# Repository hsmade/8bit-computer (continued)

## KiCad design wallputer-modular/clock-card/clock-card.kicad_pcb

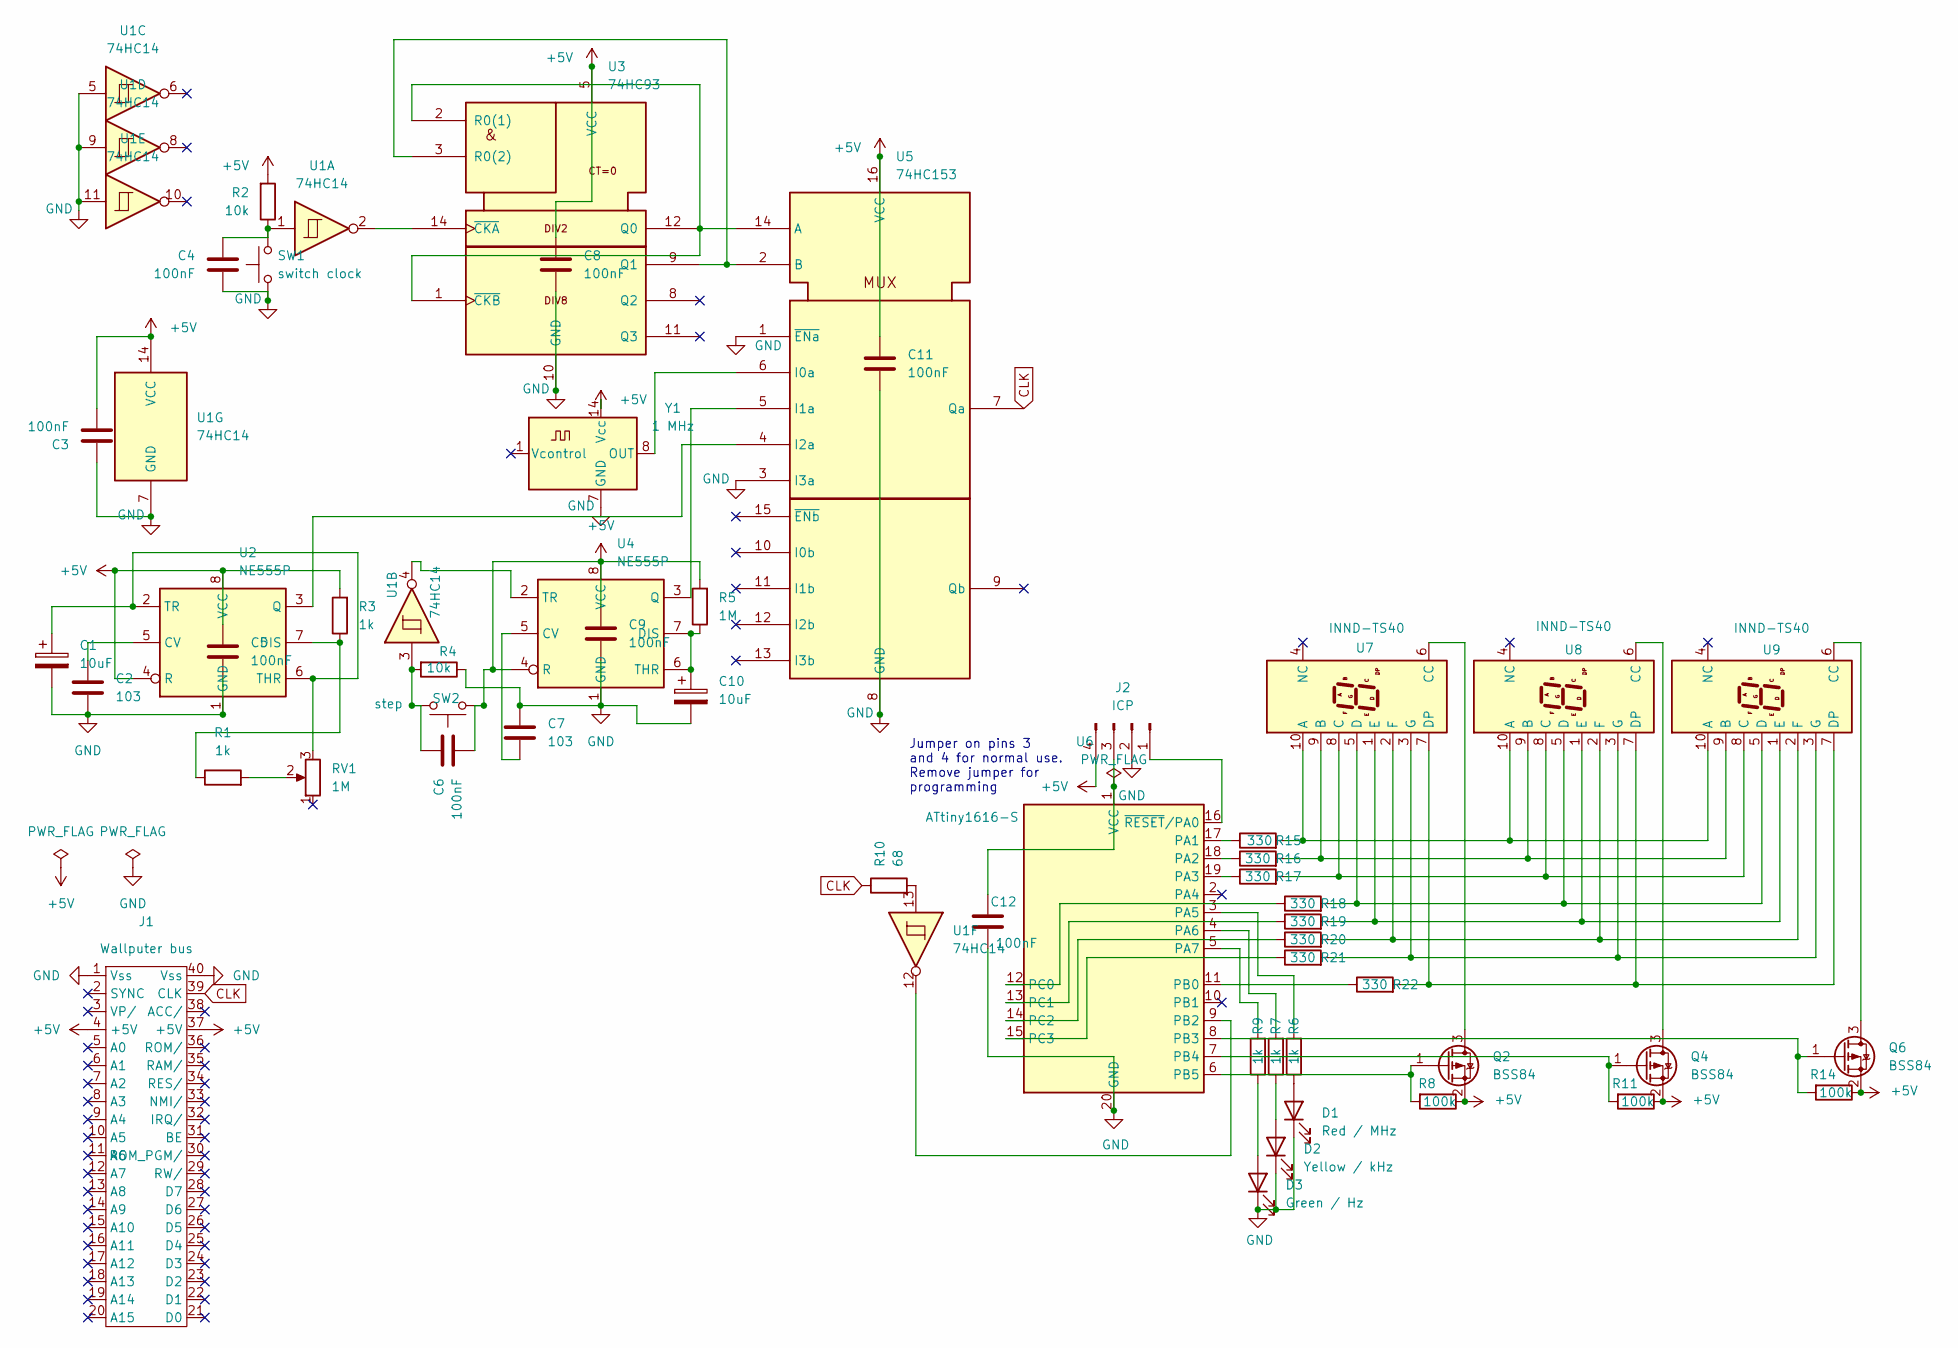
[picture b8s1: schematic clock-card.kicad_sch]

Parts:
C1, C10: 10uF; CP_Radial_D5.0mm_P2.00mm
C2, C7: 103; C_Disc_D5.0mm_W2.5mm_P5.00mm
C3, C4, C5, C6, C8, C9, C11, C12: 100nF; C_Disc_D5.0mm_W2.5mm_P5.00mm
D1: Red / MHz; LED_D1.8mm_W3.3mm_H2.4mm
D2: Yellow / kHz; LED_D1.8mm_W3.3mm_H2.4mm
D3: Green / Hz; LED_D1.8mm_W3.3mm_H2.4mm
J1: Wallputer_Bus_*
J2: ICP; PinHeader_1x04_P2.54mm_Vertical
Q2, Q4, Q6: BSS84; SOT-23
R1, R3: 1k; R_Axial_DIN0204_L3.6mm_D1.6mm_P2.54mm_Vertical
R2, R4: 10k; R_Axial_DIN0204_L3.6mm_D1.6mm_P2.54mm_Vertical
R5: 1M; R_Axial_DIN0204_L3.6mm_D1.6mm_P2.54mm_Vertical
R6, R7, R9: 1k; R_0603_1608Metric
R8, R11, R14: 100k; R_0603_1608Metric
R10: 68; R_0603_1608Metric
R15, R16, R17, R18, R19, R20, R21, R22: 330; R_0603_1608Metric
RV1: 1M; Potentiometer_Alpha_RD901F-40-00D_Single_Vertical
SW1: switch clock; SW_PUSH_6mm_H4.3mm
SW2: step; SW_PUSH_6mm_H4.3mm
U1: 74HC14; DIP-14_W7.62mm_Socket
U2, U4: NE555P; DIP-8_W7.62mm
U3: 74HC93; DIP-14_W7.62mm_Socket
U5: 74HC153; DIP-16_W7.62mm_Socket
U6: ATtiny1616-S; SOIC-20W_7.5x12.8mm_P1.27mm
U7, U8, U9: INND-TS40
Y1: 1 MHz; Oscillator_DIP-14

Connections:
+5V: C3.2, C5.1, C6.2, C8.1, C9.1, C11.1, J1.4 (+5V), J1.37 (+5V), J2.4, Q2.2 (S), Q4.2 (S), Q6.2 (S), R2.2, R3.2, R5.2, R8.1, R11.1, R14.1, SW2.1, U1.14 (VCC), U2.4 (R), U2.8 (VCC), U3.5 (VCC), U4.4 (R), U4.8 (VCC), U5.16 (VCC), Y1.14 (Vcc)
CLK: J1.39 (CLK), R10.1, U5.7 (Qa)
GND: C1.2, C2.2, C3.1, C4.2, C5.2, C7.1, C8.2, C9.2, C10.2, C11.2, C12.2, D1.1 (K), D2.1 (K), D3.1 (K), J1.1 (Vss), J1.40 (Vss), J2.2, R4.1, SW1.1, U1.5, U1.7 (GND), U1.9, U1.11, U2.1 (GND), U3.10 (GND), U4.1 (GND), U5.1 (~ENa), U5.3 (I3a), U5.8 (GND), U6.20 (GND), Y1.7 (GND)
unnamed: C4.1, R2.1, SW1.2, U1.1
unnamed: C6.1, R4.2, SW2.2, U1.3
unnamed: D1.2 (A), R6.1
unnamed: D2.2 (A), R7.1
unnamed: D3.2 (A), R9.1
unnamed: J2.1, U6.16 (~RESET/PA0)
unnamed: C12.1, J2.3, U6.1 (VCC)
unnamed: Q2.3 (D), U7.6 (CC)
unnamed: Q2.1 (G), R8.2, U6.6 (PB5)
unnamed: Q4.3 (D), U8.6 (CC)
unnamed: Q4.1 (G), R11.2, U6.7 (PB4)
unnamed: Q6.3 (D), U9.6 (CC)
unnamed: Q6.1 (G), R14.2, U6.8 (PB3)
unnamed: R1.2, RV1.2
unnamed: R10.2, U1.13
unnamed: C2.1, U2.5 (CV)
unnamed: R1.1, R3.1, U2.7 (DIS)
unnamed: U2.3 (Q), U5.4 (I2a)
unnamed: C1.1, RV1.3, U2.2 (TR), U2.6 (THR)
unnamed: U3.1 (~CKB), U3.2 (R0(1)), U3.12 (Q0), U5.14 (A)
unnamed: U3.3 (R0(2)), U3.9 (Q1), U5.2 (B)
unnamed: U1.2, U3.14 (~CKA)
unnamed: C7.2, U4.5 (CV)
unnamed: C10.1, R5.1, U4.6 (THR), U4.7 (DIS)
unnamed: U4.3 (Q), U5.5 (I1a)
unnamed: U1.4, U4.2 (TR)
unnamed: U5.6 (I0a), Y1.8 (OUT)
unnamed: R15.1, U6.17 (PA1)
unnamed: R16.1, U6.18 (PA2)
unnamed: R17.1, U6.19 (PA3)
unnamed: R6.2, U6.3 (PA5)
unnamed: R7.2, U6.4 (PA6)
unnamed: R9.2, U6.5 (PA7)
unnamed: R22.1, U6.11 (PB0)
unnamed: U1.12, U6.9 (PB2)
unnamed: R18.1, U6.12 (PC0)
unnamed: R19.1, U6.13 (PC1)
unnamed: R20.1, U6.14 (PC2)
unnamed: R21.1, U6.15 (PC3)
unnamed: R15.2, U7.10 (A), U8.10 (A), U9.10 (A)
unnamed: R16.2, U7.9 (B), U8.9 (B), U9.9 (B)
unnamed: R17.2, U7.8 (C), U8.8 (C), U9.8 (C)
unnamed: R18.2, U7.5 (D), U8.5 (D), U9.5 (D)
unnamed: R22.2, U7.7 (DP), U8.7 (DP), U9.7 (DP)
unnamed: R19.2, U7.1 (E), U8.1 (E), U9.1 (E)
unnamed: R20.2, U7.2 (F), U8.2 (F), U9.2 (F)
unnamed: R21.2, U7.3 (G), U8.3 (G), U9.3 (G)

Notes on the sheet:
Jumper on pins 3 and 4 for normal use. Remove jumper for programming

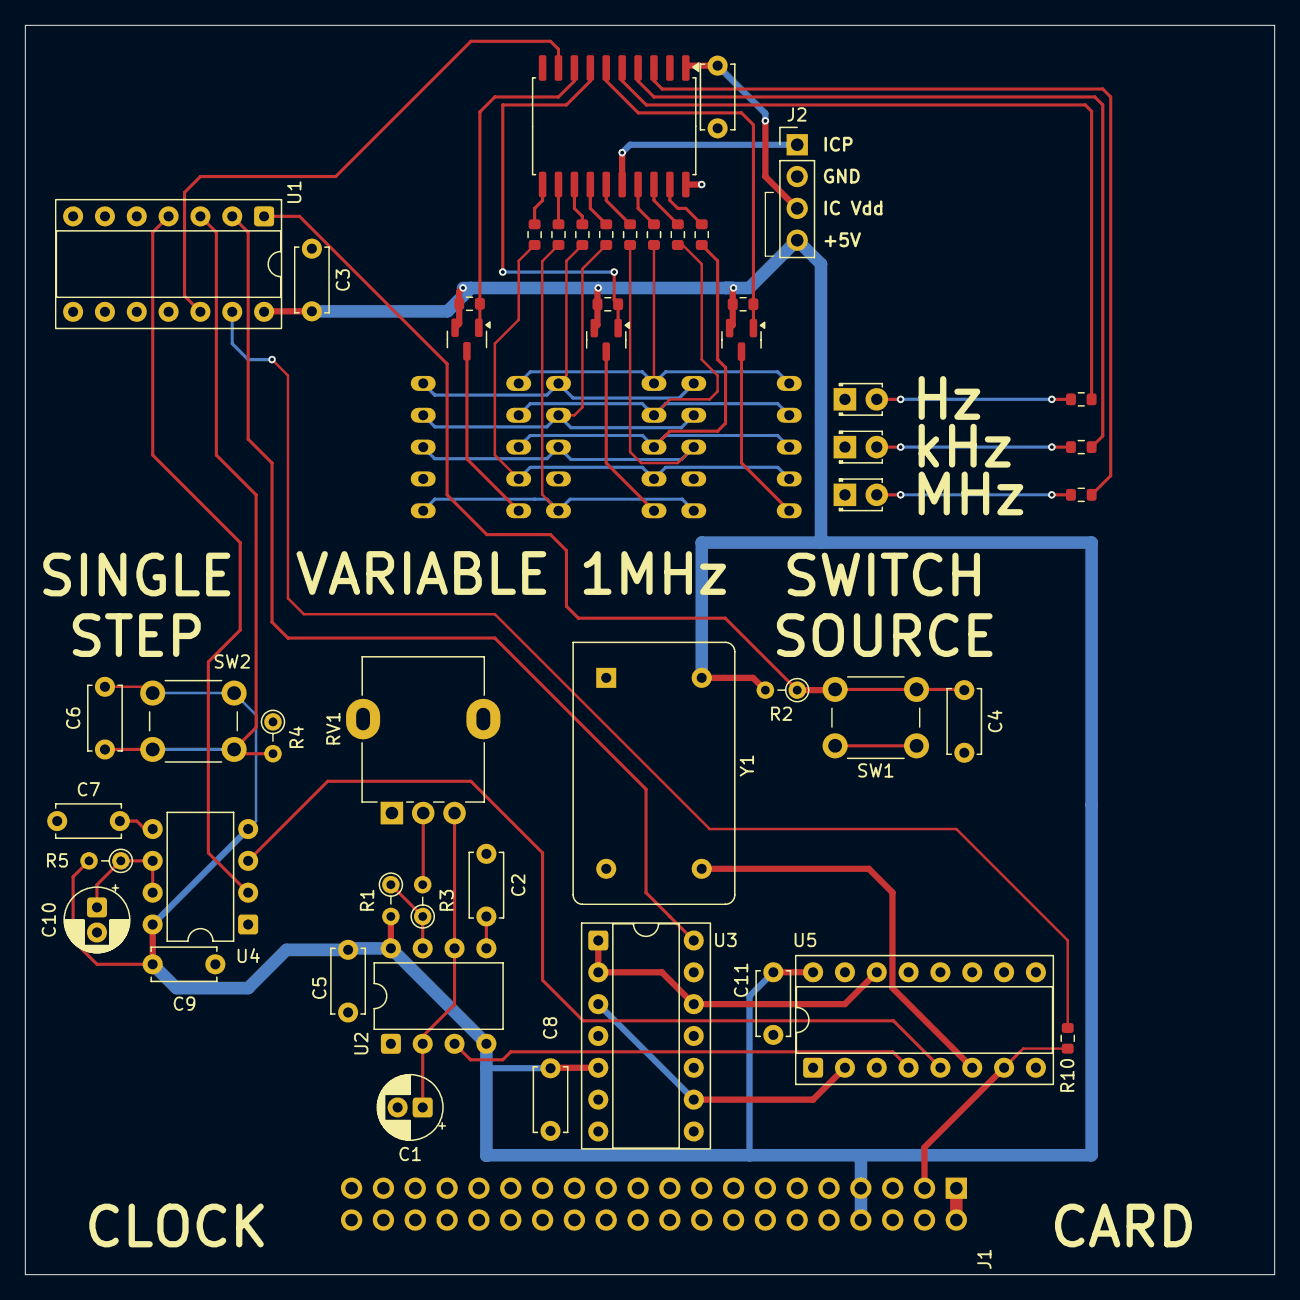
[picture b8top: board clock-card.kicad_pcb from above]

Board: 2 copper layers, 99.7 x 99.7 mm, 53 parts (0 on the bottom side), 50 nets.

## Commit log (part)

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2022-04-04 initial
2022-04-04 bugfix
2022-04-04 fixes, issue with firmware vectors
2022-04-05 refactor
2022-04-06 added schema
2022-04-07 let logic handle the OE and CE
2022-04-07 fix eeprom writing
2022-04-09 fix program loop; new board
2022-04-11 fix memmory range
2022-04-14 add firmware for address decoder
2022-04-14 add address display kicad
2022-04-14 add bus
2022-04-14 add usage
2022-04-14 add pcb
2022-04-17 refactor repo
2022-04-17 add build log
2022-04-18 finished bus display
2022-04-18 update rom image
2022-04-18 move build log to docs
2022-04-18 Set theme jekyll-theme-hacker
2022-04-18 adding datasheets
2022-04-18 spacing
2022-04-18 docs cleanup
2022-04-18 change around links
2022-04-18 add CPU to docs
2022-04-18 fix docs
2022-04-19 move docs back into source tree
2022-04-19 test includes
2022-04-19 fix image links
2022-04-19 fix paths
2022-04-21 added cpu mock
2022-04-21 shrink images
2022-04-21 update cpu-mock image
2022-04-21 document CPU board idea
2022-05-09 update docs
2022-05-09 add chapters as files
2022-05-09 add new chapter
2022-05-09 fix links
2022-07-07 update ROM board; add log
2022-07-30 add bits
2022-07-30 fix build; fix 0xFF; add missing kicad
2022-07-31 update some docs/comments
2024-11-09 serial echo
